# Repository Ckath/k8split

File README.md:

shoddy split keyboard for personal use, after ruining my [chinese split keyboard](http://xahlee.info/kbd/ly092_mini_keyboard.html) I attempted to recreate what I wanted from that, minus all the annoyances.

for the previous more scuffed and QMK version see [rev0.1](https://github.com/Ckath/k8split/tree/rev0.1)

## features
-  *normal* layout: 
	- no ortho
	- no lack of function row
	- no weird thumbclusters
	- plenty bonus keys to add what you miss
- no case or plate, only M3 holes
- halves are linked hardwired to central controller (over VGA)
- regular FULL SIZED USB PORT
- powered by TMK

## rev0.1->0.2 up/downgrades
- no more dual mcu nonsense
- no more QMK I'm not dealing with modern QMK
- no more smd 4 pin crystal suffering
- due to lack of pcb stabilizers for this formfactor: no more stabilizers
- cherry low profile switches
- boards themselves optimized for liquid damage mitigation, all throughhole for easy fixing

## pics
### keyboards
TODO
<!--  -->
<!--  -->
### pcb 
TODO
<!--  -->

## ordering
theres an `ORDER` folder in the pcb project, with all required files, dont honestly. if you want one I could probably send you one of my spare PCBs

### advice
keep in mind this is a personal board made just for myself, it's more up for reference/show than it is meant for people to actually use it. that said, some advice if you do think about making one:
- any still configured component part number is not updated, rev0.2 is made from what I had laying around and non pre assembled pcb
- to keep things easy I recommend a flat profile keycap set like dsa
- the nearly fully smd usb connector is a china find, you can find them on the regular places as "smd usb a female", the right ones should only have one shield pad on either side.
- the 'case' hardware used is a standard M3 standoff set, anything works.

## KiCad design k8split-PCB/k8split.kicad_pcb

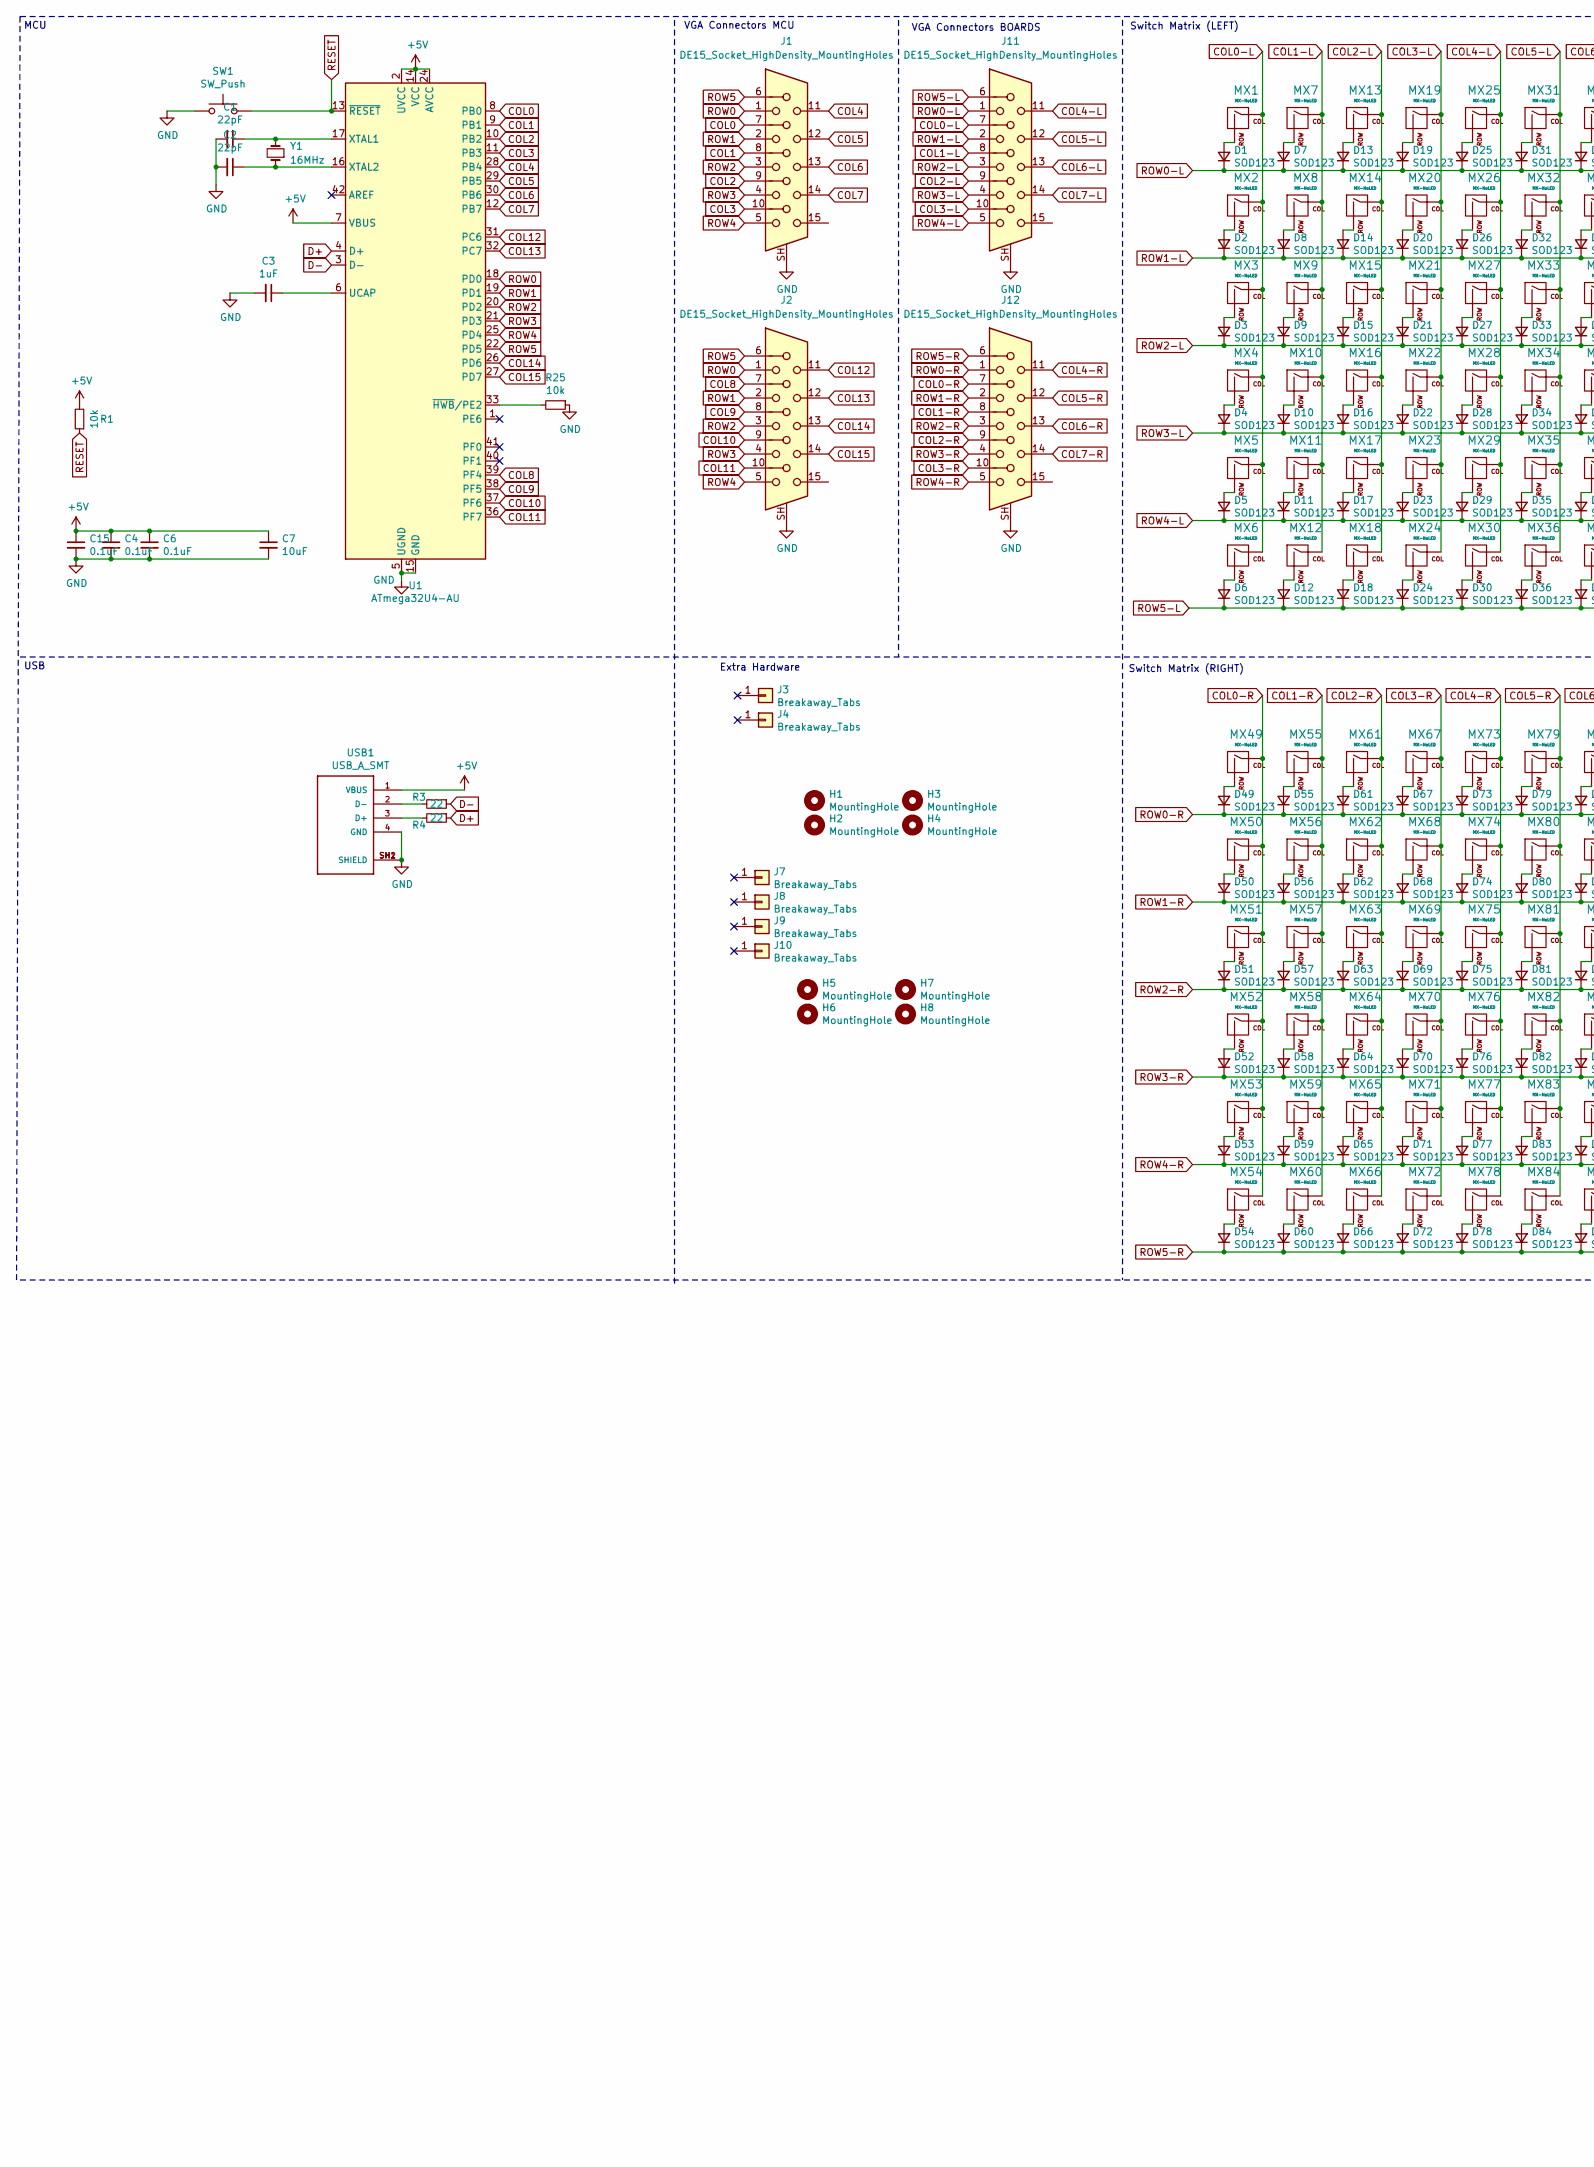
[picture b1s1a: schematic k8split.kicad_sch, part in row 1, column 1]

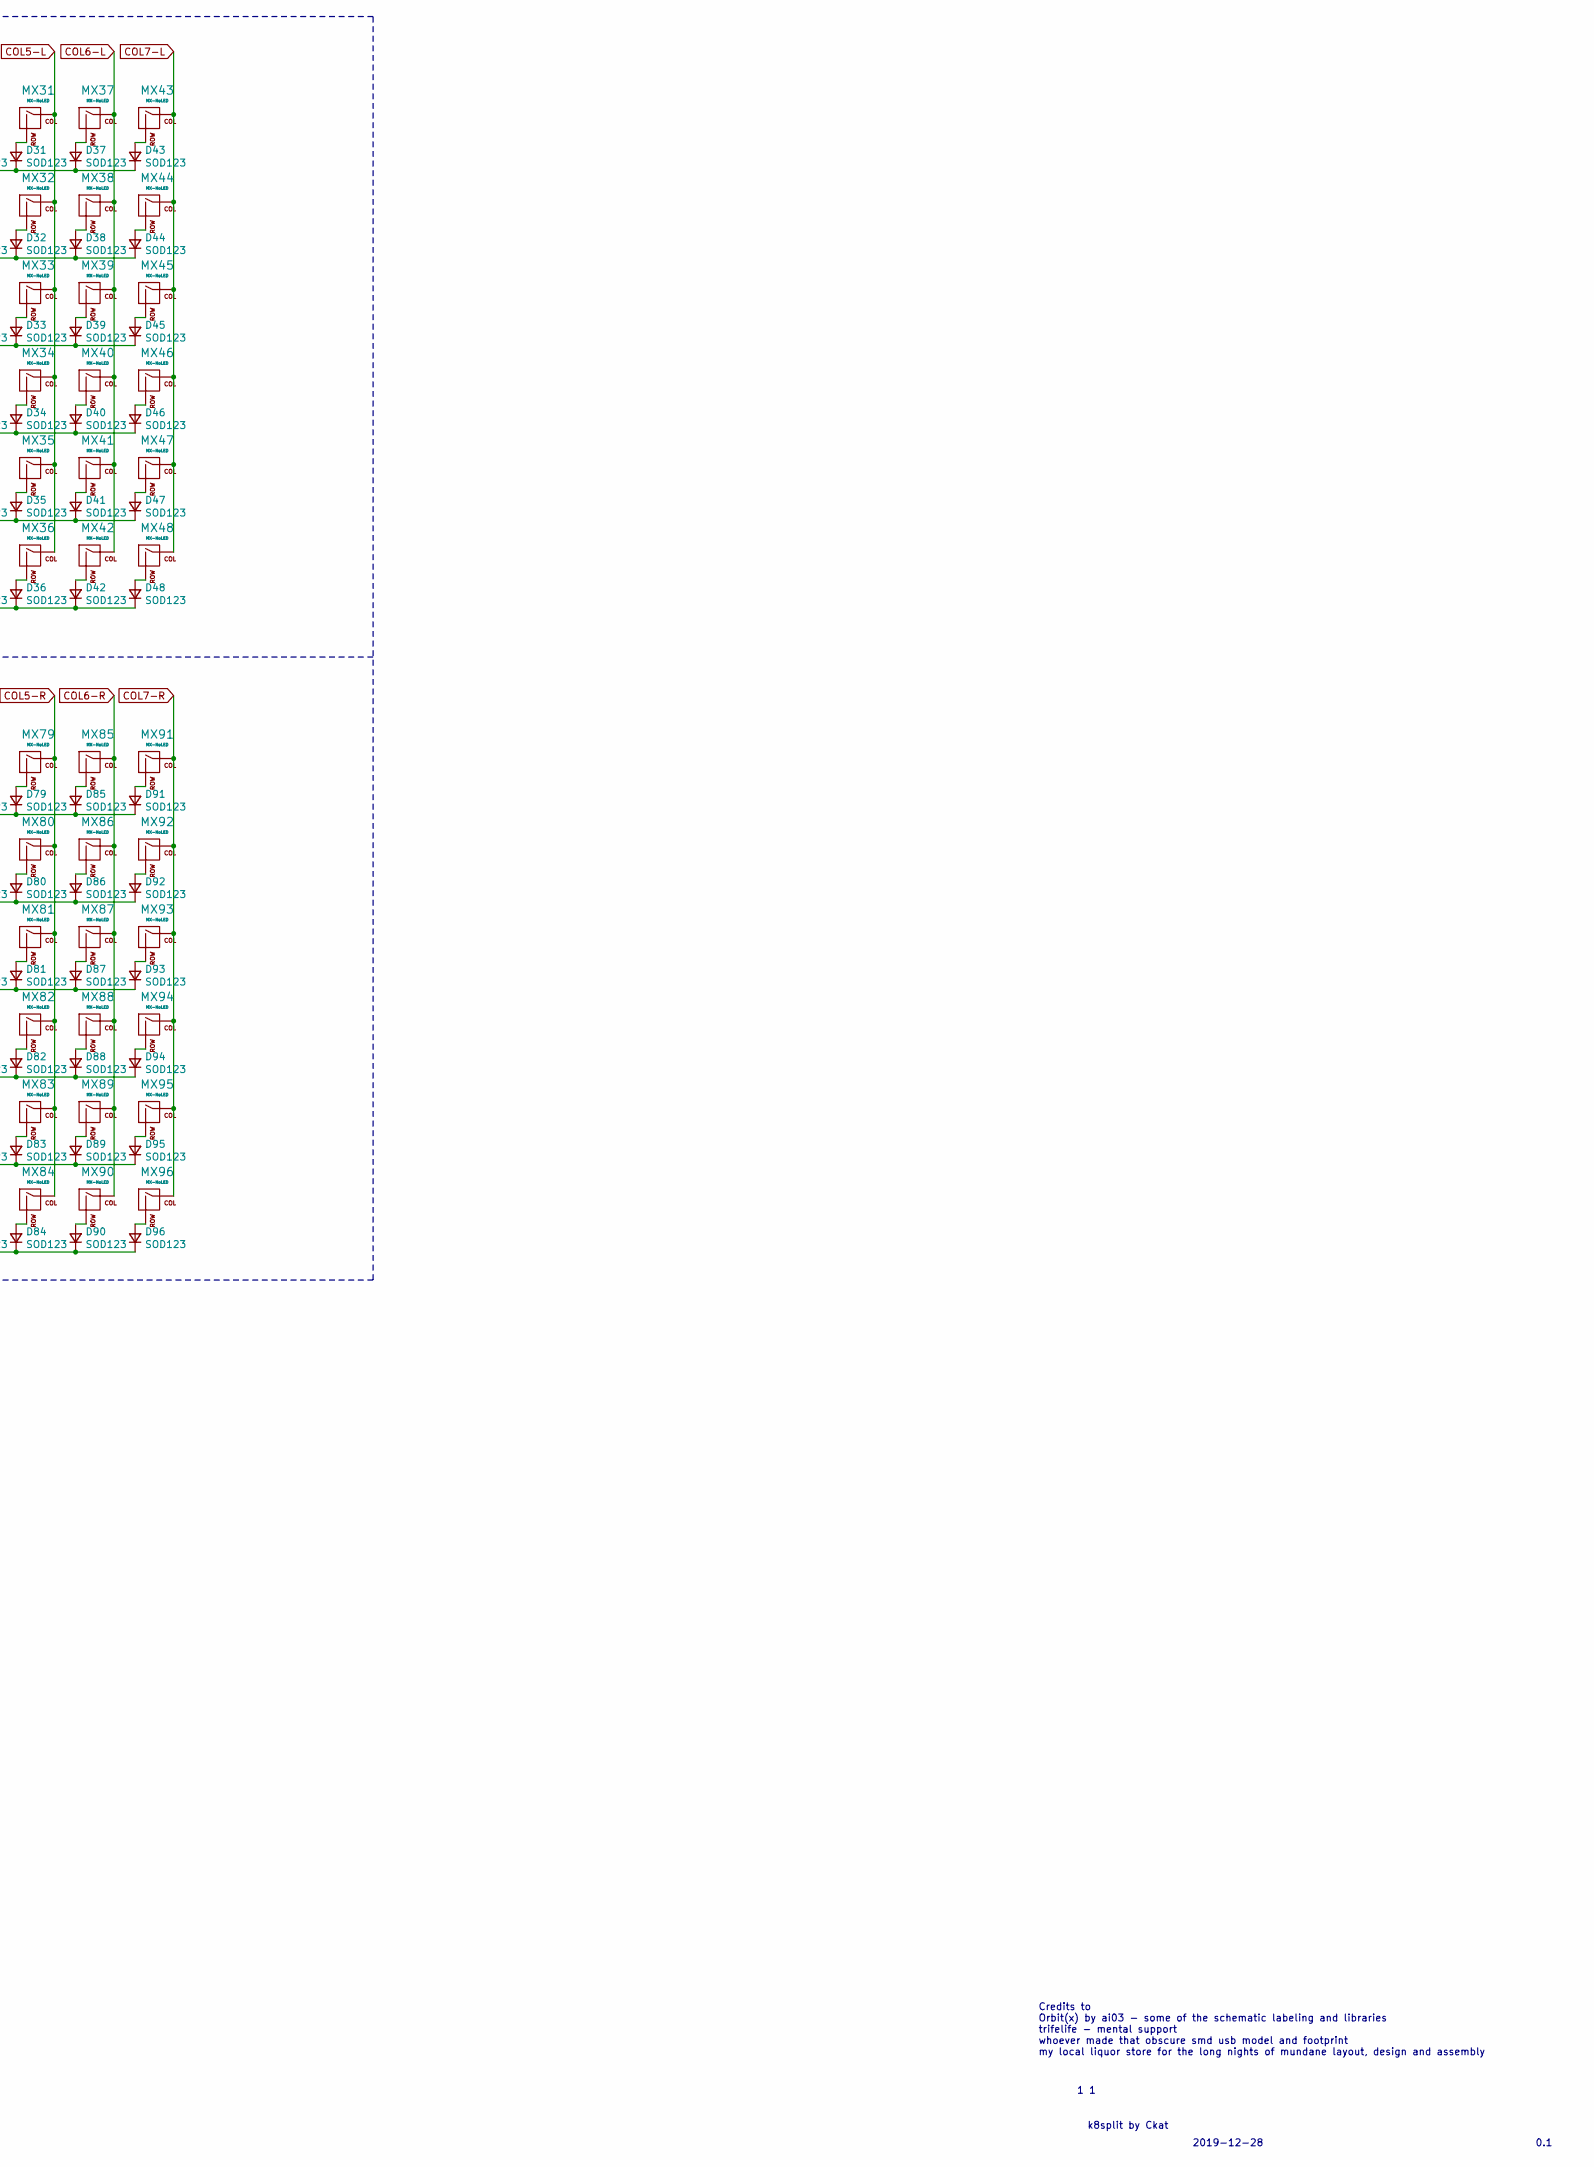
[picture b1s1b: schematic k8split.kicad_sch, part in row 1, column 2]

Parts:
C1, C2: 22pF; C_0603_1608Metric
C3: 1uF; C_0603_1608Metric
C4, C6, C15: 0.1uF; C_0603_1608Metric
C7: 10uF; C_0603_1608Metric
D1, D2, D3, D4, D5, D6, D7, D8, D9, D10, D11, D12, D13, D14, D15, D16, D17, D18, D19, D20, D21, D22, D23, D24, D25, D26, D27, D28, D29, D30, D31, D32, D33, D34, D35, D36, D37, D38, D39, D40, D41, D42, D43, D44, D45, D46, D47, D48, D49, D50, D51, D52, D53, D54, D55, D56, D57, D58, D59, D60, D61, D62, D63, D64, D65, D66, D67, D68, D69, D70, D71, D72, D73, D74, D75, D76, D77, D78, D79, D80, D81, D82, D83, D84, D85, D86, D87, D88, D89, D90, D91, D92, D93, D94, D95, D96: SOD123; D_A-405_P10.16mm_Horizontal
H1, H2, H3, H4, H5, H6, H7, H8: MountingHole; MountingHole_3.2mm_M3
J1, J2, J11, J12: DE15_Socket_HighDensity_MountingHoles; DSUB-15-HD_Socket_Horizontal_P2.29x1.90mm_EdgePinOffset3.03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
J3, J4, J7, J8, J9, J10: Breakaway_Tabs; breakaway-mousebites
MX1, MX2, MX7, MX8, MX9, MX10, MX11, MX12, MX13, MX14, MX15, MX16, MX17, MX18, MX19, MX20, MX21, MX22, MX23, MX25, MX26, MX27, MX28, MX29, MX31, MX32, MX33, MX34, MX35, MX36, MX37, MX38, MX39, MX40, MX41, MX42, MX43, MX44, MX45, MX46, MX47, MX48, MX49, MX50, MX51, MX52, MX53, MX54, MX55, MX56, MX57, MX58, MX59, MX61, MX62, MX63, MX64, MX65, MX67, MX68, MX69, MX70, MX71, MX72, MX73, MX74, MX75, MX76, MX77, MX78, MX79, MX80, MX81, MX82, MX83, MX84, MX85, MX86, MX87, MX88, MX89, MX90, MX91: MX-NoLED; SW_choc_v2_1u
MX3, MX6, MX93, MX96: MX-NoLED; SW_choc_v2_1.5u
MX4: MX-NoLED; SW_choc_v2_1.75u
MX5, MX30, MX60, MX94: MX-NoLED; SW_choc_v2_2.25u
MX24, MX66: MX-NoLED; SW_choc_v2_1.25u
MX92: MX-NoLED; SW_choc_v2_2u
MX95: MX-NoLED; SW_choc_v2_2.75u
R1, R25: 10k; R_0603_1608Metric
R3, R4: 22; R_0603_1608Metric
SW1: SW_Push; SKQGADE010
U1: ATmega32U4-AU; TQFP-44_10x10mm_P0.8mm
USB1: USB_A_SMT; CUI_UJ2-AH-4-SMT
Y1: 16MHz; Crystal_HC49-4H_Vertical

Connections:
+5V: C4.1, C6.1, C7.1, C15.1, R1.2, U1.2 (UVCC), U1.7 (VBUS), U1.14 (VCC), U1.24 (AVCC), U1.34 (VCC), U1.44 (AVCC), USB1.1 (VBUS)
COL0: J1.7, U1.8 (PB0)
COL0-L: J11.7, MX1.1 (COL), MX2.1 (COL), MX3.1 (COL), MX4.1 (COL), MX5.1 (COL), MX6.1 (COL)
COL0-R: J12.7, MX49.1 (COL), MX50.1 (COL), MX51.1 (COL), MX52.1 (COL), MX53.1 (COL), MX54.1 (COL)
COL1: J1.8, U1.9 (PB1)
COL1-L: J11.8, MX7.1 (COL), MX8.1 (COL), MX9.1 (COL), MX10.1 (COL), MX11.1 (COL), MX12.1 (COL)
COL1-R: J12.8, MX55.1 (COL), MX56.1 (COL), MX57.1 (COL), MX58.1 (COL), MX59.1 (COL), MX60.1 (COL)
COL2: J1.9, U1.10 (PB2)
COL2-L: J11.9, MX13.1 (COL), MX14.1 (COL), MX15.1 (COL), MX16.1 (COL), MX17.1 (COL), MX18.1 (COL)
COL2-R: J12.9, MX61.1 (COL), MX62.1 (COL), MX63.1 (COL), MX64.1 (COL), MX65.1 (COL), MX66.1 (COL)
COL3: J1.10, U1.11 (PB3)
COL3-L: J11.10, MX19.1 (COL), MX20.1 (COL), MX21.1 (COL), MX22.1 (COL), MX23.1 (COL), MX24.1 (COL)
COL3-R: J12.10, MX67.1 (COL), MX68.1 (COL), MX69.1 (COL), MX70.1 (COL), MX71.1 (COL), MX72.1 (COL)
COL4: J1.11, U1.28 (PB4)
COL4-L: J11.11, MX25.1 (COL), MX26.1 (COL), MX27.1 (COL), MX28.1 (COL), MX29.1 (COL), MX30.1 (COL)
COL4-R: J12.11, MX73.1 (COL), MX74.1 (COL), MX75.1 (COL), MX76.1 (COL), MX77.1 (COL), MX78.1 (COL)
COL5: J1.12, U1.29 (PB5)
COL5-L: J11.12, MX31.1 (COL), MX32.1 (COL), MX33.1 (COL), MX34.1 (COL), MX35.1 (COL), MX36.1 (COL)
COL5-R: J12.12, MX79.1 (COL), MX80.1 (COL), MX81.1 (COL), MX82.1 (COL), MX83.1 (COL), MX84.1 (COL)
COL6: J1.13, U1.30 (PB6)
COL6-L: J11.13, MX37.1 (COL), MX38.1 (COL), MX39.1 (COL), MX40.1 (COL), MX41.1 (COL), MX42.1 (COL)
COL6-R: J12.13, MX85.1 (COL), MX86.1 (COL), MX87.1 (COL), MX88.1 (COL), MX89.1 (COL), MX90.1 (COL)
COL7: J1.14, U1.12 (PB7)
COL7-L: J11.14, MX43.1 (COL), MX44.1 (COL), MX45.1 (COL), MX46.1 (COL), MX47.1 (COL), MX48.1 (COL)
COL7-R: J12.14, MX91.1 (COL), MX92.1 (COL), MX93.1 (COL), MX94.1 (COL), MX95.1 (COL), MX96.1 (COL)
COL8: J2.7, U1.39 (PF4)
COL9: J2.8, U1.38 (PF5)
COL10: J2.9, U1.37 (PF6)
COL11: J2.10, U1.36 (PF7)
COL12: J2.11, U1.31 (PC6)
COL13: J2.12, U1.32 (PC7)
COL14: J2.13, U1.26 (PD6)
COL15: J2.14, U1.27 (PD7)
D+: R4.1, U1.4 (D+)
D-: R3.1, U1.3 (D-)
GND: C1.2, C2.2, C3.2, C4.2, C6.2, C7.2, C15.2, J1.SH, J2.SH, J11.SH, J12.SH, R25.1, SW1.1, U1.5 (UGND), U1.15 (GND), U1.23 (GND), U1.35 (GND), U1.43 (GND), USB1.4 (GND), USB1.SH1 (SHIELD), USB1.SH2 (SHIELD)
unnamed: D1.2 (A), MX1.2 (ROW)
unnamed: D2.2 (A), MX2.2 (ROW)
unnamed: D3.2 (A), MX3.2 (ROW)
unnamed: D4.2 (A), MX4.2 (ROW)
unnamed: D5.2 (A), MX5.2 (ROW)
unnamed: D6.2 (A), MX6.2 (ROW)
unnamed: D7.2 (A), MX7.2 (ROW)
unnamed: D8.2 (A), MX8.2 (ROW)
unnamed: D9.2 (A), MX9.2 (ROW)
unnamed: D10.2 (A), MX10.2 (ROW)
unnamed: D11.2 (A), MX11.2 (ROW)
unnamed: D12.2 (A), MX12.2 (ROW)
unnamed: D13.2 (A), MX13.2 (ROW)
unnamed: D14.2 (A), MX14.2 (ROW)
unnamed: D15.2 (A), MX15.2 (ROW)
unnamed: D16.2 (A), MX16.2 (ROW)
unnamed: D17.2 (A), MX17.2 (ROW)
unnamed: D18.2 (A), MX18.2 (ROW)
unnamed: D19.2 (A), MX19.2 (ROW)
unnamed: D20.2 (A), MX20.2 (ROW)
unnamed: D21.2 (A), MX21.2 (ROW)
unnamed: D22.2 (A), MX22.2 (ROW)
unnamed: D23.2 (A), MX23.2 (ROW)
unnamed: D24.2 (A), MX24.2 (ROW)
unnamed: D25.2 (A), MX25.2 (ROW)
unnamed: D26.2 (A), MX26.2 (ROW)
unnamed: D27.2 (A), MX27.2 (ROW)
unnamed: D28.2 (A), MX28.2 (ROW)
unnamed: D29.2 (A), MX29.2 (ROW)
unnamed: D30.2 (A), MX30.2 (ROW)
unnamed: D31.2 (A), MX31.2 (ROW)
unnamed: D32.2 (A), MX32.2 (ROW)
unnamed: D33.2 (A), MX33.2 (ROW)
unnamed: D34.2 (A), MX34.2 (ROW)
unnamed: D35.2 (A), MX35.2 (ROW)
unnamed: D36.2 (A), MX36.2 (ROW)
unnamed: D37.2 (A), MX37.2 (ROW)
unnamed: D38.2 (A), MX38.2 (ROW)
unnamed: D39.2 (A), MX39.2 (ROW)
unnamed: D40.2 (A), MX40.2 (ROW)
unnamed: D41.2 (A), MX41.2 (ROW)
unnamed: D42.2 (A), MX42.2 (ROW)
unnamed: D43.2 (A), MX43.2 (ROW)
unnamed: D44.2 (A), MX44.2 (ROW)
unnamed: D45.2 (A), MX45.2 (ROW)
unnamed: D46.2 (A), MX46.2 (ROW)
unnamed: D47.2 (A), MX47.2 (ROW)
unnamed: D48.2 (A), MX48.2 (ROW)
unnamed: D49.2 (A), MX49.2 (ROW)
unnamed: D50.2 (A), MX50.2 (ROW)
unnamed: D51.2 (A), MX51.2 (ROW)
unnamed: D52.2 (A), MX52.2 (ROW)
unnamed: D53.2 (A), MX53.2 (ROW)
unnamed: D54.2 (A), MX54.2 (ROW)
unnamed: D55.2 (A), MX55.2 (ROW)
unnamed: D56.2 (A), MX56.2 (ROW)
unnamed: D57.2 (A), MX57.2 (ROW)
unnamed: D58.2 (A), MX58.2 (ROW)
unnamed: D59.2 (A), MX59.2 (ROW)
unnamed: D60.2 (A), MX60.2 (ROW)
unnamed: D61.2 (A), MX61.2 (ROW)
unnamed: D62.2 (A), MX62.2 (ROW)
unnamed: D63.2 (A), MX63.2 (ROW)
unnamed: D64.2 (A), MX64.2 (ROW)
unnamed: D65.2 (A), MX65.2 (ROW)
unnamed: D66.2 (A), MX66.2 (ROW)
unnamed: D67.2 (A), MX67.2 (ROW)
unnamed: D68.2 (A), MX68.2 (ROW)
unnamed: D69.2 (A), MX69.2 (ROW)
unnamed: D70.2 (A), MX70.2 (ROW)
unnamed: D71.2 (A), MX71.2 (ROW)
unnamed: D72.2 (A), MX72.2 (ROW)
unnamed: D73.2 (A), MX73.2 (ROW)
unnamed: D74.2 (A), MX74.2 (ROW)
unnamed: D75.2 (A), MX75.2 (ROW)
unnamed: D76.2 (A), MX76.2 (ROW)
unnamed: D77.2 (A), MX77.2 (ROW)
unnamed: D78.2 (A), MX78.2 (ROW)
unnamed: D79.2 (A), MX79.2 (ROW)
unnamed: D80.2 (A), MX80.2 (ROW)
unnamed: D81.2 (A), MX81.2 (ROW)
unnamed: D82.2 (A), MX82.2 (ROW)
unnamed: D83.2 (A), MX83.2 (ROW)
unnamed: D84.2 (A), MX84.2 (ROW)
unnamed: D85.2 (A), MX85.2 (ROW)
unnamed: D86.2 (A), MX86.2 (ROW)
unnamed: D87.2 (A), MX87.2 (ROW)
unnamed: D88.2 (A), MX88.2 (ROW)
unnamed: D89.2 (A), MX89.2 (ROW)
unnamed: D90.2 (A), MX90.2 (ROW)
unnamed: D91.2 (A), MX91.2 (ROW)
unnamed: D92.2 (A), MX92.2 (ROW)
unnamed: D93.2 (A), MX93.2 (ROW)
unnamed: D94.2 (A), MX94.2 (ROW)
unnamed: D95.2 (A), MX95.2 (ROW)
unnamed: D96.2 (A), MX96.2 (ROW)
unnamed: C3.1, U1.6 (UCAP)
unnamed: C1.1, U1.17 (XTAL1), Y1.2
unnamed: C2.1, U1.16 (XTAL2), Y1.1
unnamed: R25.2, U1.33 (~HWB/PE2)
unnamed: R4.2, USB1.3 (D+)
unnamed: R3.2, USB1.2 (D-)
RESET: R1.1, SW1.2, U1.13 (~RESET)
ROW0: J1.1, J2.1, U1.18 (PD0)
ROW0-L: D1.1 (K), D7.1 (K), D13.1 (K), D19.1 (K), D25.1 (K), D31.1 (K), D37.1 (K), D43.1 (K), J11.1
ROW0-R: D49.1 (K), D55.1 (K), D61.1 (K), D67.1 (K), D73.1 (K), D79.1 (K), D85.1 (K), D91.1 (K), J12.1
ROW1: J1.2, J2.2, U1.19 (PD1)
ROW1-L: D2.1 (K), D8.1 (K), D14.1 (K), D20.1 (K), D26.1 (K), D32.1 (K), D38.1 (K), D44.1 (K), J11.2
ROW1-R: D50.1 (K), D56.1 (K), D62.1 (K), D68.1 (K), D74.1 (K), D80.1 (K), D86.1 (K), D92.1 (K), J12.2
ROW2: J1.3, J2.3, U1.20 (PD2)
ROW2-L: D3.1 (K), D9.1 (K), D15.1 (K), D21.1 (K), D27.1 (K), D33.1 (K), D39.1 (K), D45.1 (K), J11.3
ROW2-R: D51.1 (K), D57.1 (K), D63.1 (K), D69.1 (K), D75.1 (K), D81.1 (K), D87.1 (K), D93.1 (K), J12.3
ROW3: J1.4, J2.4, U1.21 (PD3)
ROW3-L: D4.1 (K), D10.1 (K), D16.1 (K), D22.1 (K), D28.1 (K), D34.1 (K), D40.1 (K), D46.1 (K), J11.4
ROW3-R: D52.1 (K), D58.1 (K), D64.1 (K), D70.1 (K), D76.1 (K), D82.1 (K), D88.1 (K), D94.1 (K), J12.4
ROW4: J1.5, J2.5, U1.25 (PD4)
ROW4-L: D5.1 (K), D11.1 (K), D17.1 (K), D23.1 (K), D29.1 (K), D35.1 (K), D41.1 (K), D47.1 (K), J11.5
ROW4-R: D53.1 (K), D59.1 (K), D65.1 (K), D71.1 (K), D77.1 (K), D83.1 (K), D89.1 (K), D95.1 (K), J12.5
ROW5: J1.6, J2.6, U1.22 (PD5)
ROW5-L: D6.1 (K), D12.1 (K), D18.1 (K), D24.1 (K), D30.1 (K), D36.1 (K), D42.1 (K), D48.1 (K), J11.6
ROW5-R: D54.1 (K), D60.1 (K), D66.1 (K), D72.1 (K), D78.1 (K), D84.1 (K), D90.1 (K), D96.1 (K), J12.6

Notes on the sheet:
VGA Connectors BOARDS
VGA Connectors MCU
Extra Hardware
Credits to Orbit(x) by ai03 - some of the schematic labeling and libraries trifelife - mental support whoever made that obscure smd usb model and footprint my local liquor store for the long nights of mundane layout, design and assembly
1 1
MCU
0.1
k8split by Ckat
Switch Matrix (RIGHT)
USB
2019-12-28
Switch Matrix (LEFT)

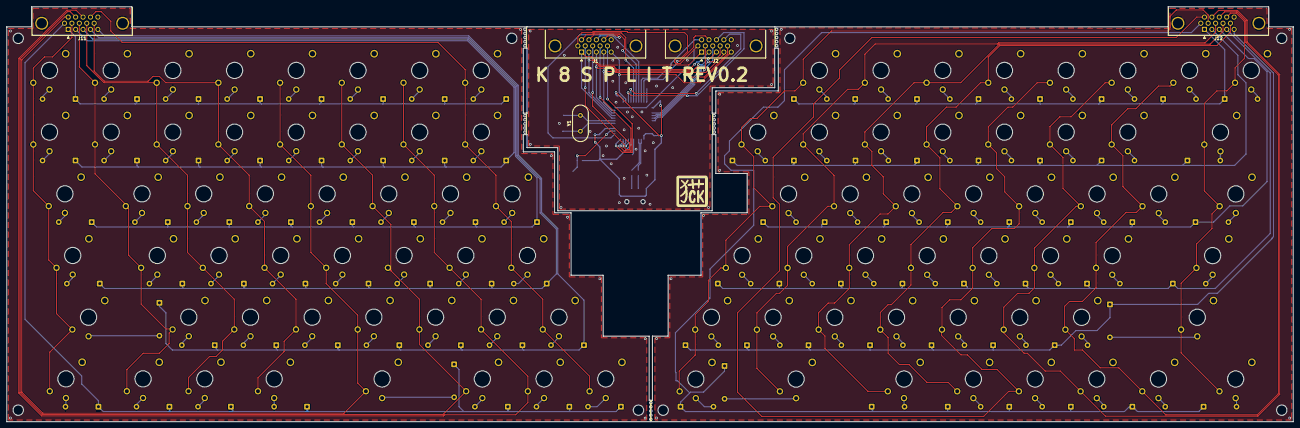
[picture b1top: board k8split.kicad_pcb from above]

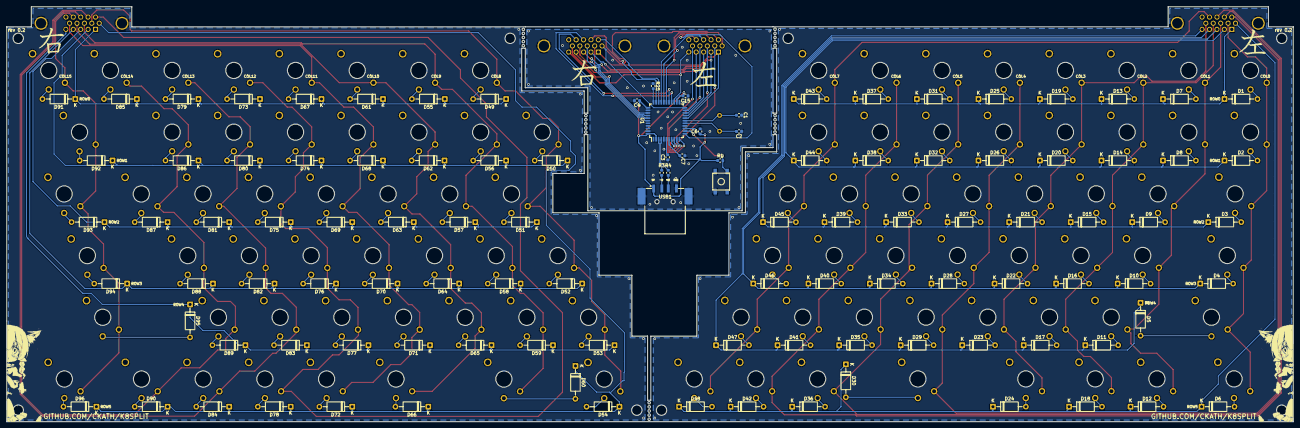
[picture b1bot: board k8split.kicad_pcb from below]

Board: 2 copper layers, 397.3 x 128.1 mm, 224 parts (110 on the bottom side), 157 nets.

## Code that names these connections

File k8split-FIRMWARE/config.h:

/* MIT License

Copyright (c) 2026 Ckat <Ckath@yandex.ru>

Permission is hereby granted, free of charge, to any person obtaining a copy
of this software and associated documentation files (the "Software"), to deal
in the Software without restriction, including without limitation the rights
to use, copy, modify, merge, publish, distribute, sublicense, and/or sell
copies of the Software, and to permit persons to whom the Software is
furnished to do so, subject to the following conditions:

The above copyright notice and this permission notice shall be included in all
copies or substantial portions of the Software.

THE SOFTWARE IS PROVIDED "AS IS", WITHOUT WARRANTY OF ANY KIND, EXPRESS OR
IMPLIED, INCLUDING BUT NOT LIMITED TO THE WARRANTIES OF MERCHANTABILITY,
FITNESS FOR A PARTICULAR PURPOSE AND NONINFRINGEMENT. IN NO EVENT SHALL THE
AUTHORS OR COPYRIGHT HOLDERS BE LIABLE FOR ANY CLAIM, DAMAGES OR OTHER
LIABILITY, WHETHER IN AN ACTION OF CONTRACT, TORT OR OTHERWISE, ARISING FROM,
OUT OF OR IN CONNECTION WITH THE SOFTWARE OR THE USE OR OTHER DEALINGS IN THE
SOFTWARE.
*/
#ifndef CONFIG_H
#define CONFIG_H

/* USB Device descriptor parameter */
#define VENDOR_ID       0xC81D
#define PRODUCT_ID      0xC868
#define DEVICE_VER      0x0002
#define MANUFACTURER    Ckat 
#define PRODUCT         k8split
#define DESCRIPTION     rev0.2

/* key matrix size */
#define MATRIX_ROWS 6
#define MATRIX_COLS 16

/* ROW/COL MASKS */
#define ROW_MASK  0b00111111 /* PD0-PD5 row0-row5 */
#define COLB_MASK 0b11111111 /* PB0-PB7 col0-col7 */
#define COLF_MASK 0b11110000 /* PF4-PF6 col8-col11 */
#define COLC_MASK 0b11000000 /* PC6-PF7 col12-col13 */
#define COLD_MASK 0b11000000 /* PD6-PD7 col14-col15 */

/* can get away with lower since silent choc v2 */
#define DEBOUNCE 3

/* disable action features */
#define NO_ACTION_LAYER
#define NO_ACTION_TAPPING
#define NO_ACTION_ONESHOT
#define NO_ACTION_MACRO
#define NO_ACTION_FUNCTION

#endif

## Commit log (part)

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2020-01-05 remove incompatible 3d file
2020-01-13 near completed routing on boards
2020-01-17 add some branding to pcb
2020-01-19 small board redesign regarding usb, start fixing silkscreen
2020-01-22 initial panelizing
2020-01-23 finish panelizing pcb
2020-01-25 initial gerber files
2020-01-26 add jlc bom, move switches
    - all part numbers found on jlc, might change some packages later
    - move switches to other side because smd manufacturing is one side
    - gerbers not regenerated, more changes to be done before doing it again
2020-01-26 cleaned up libs and parts
    - switched out 0805 resistors to 0603
    - deleted some unused libraries
    - re-associated symbols libs to point to system ones
2020-01-28 redid some silkscreen, cleaned up button move
2020-01-29 move silk on avr connectors
2020-01-31 add silk for usb pins very uuseful
2020-02-01 avr program header typesetting wwow
2020-02-10 add some corona jokes
2020-02-11 trace cleanup
2020-02-11 more trace cleanup
2020-02-17 further pcb project cleanup
2020-02-17 initial readme draft
2020-05-18 add license
2020-05-18 update some minor schmetatic details
2020-05-18 updated readme on rev 0.1 mistakes
2020-05-18 update features
2020-05-18 pics
2020-05-18 cleanup order folder
2020-05-20 add some order advice
2020-05-21 update qmk link to link directly to keyboard
